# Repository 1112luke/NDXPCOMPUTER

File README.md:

<h1 align="center">⚡️🚀Notre Dame Rocketry Flight Computer🖥️⚡️</h1>

<h2 align="center">F.E.R.B (For Every Rocketry Build) 🤓</h2>

<p align="center">
  </img>
</p>

<h4 align="center">This is the repository for the HARDWARE DESIGN ONLY. Software for the computer can be found <a href="https://github.com/1112luke/NDXP_COMPUTER_SOFTWARE">here</a></h4>

## Introduction

While initially designed and developed for NDXP, all vehicle applications were heavily considered during the process. The result is a computer that is <i>intended</i> to be used for any and all rocketry vehicles!

## Contributing
This repository is open at all times to any member submitting a Pull Request and merging their code directly into the main branch after approval! If you don't know what a Pull Request is, or if this is your first time using github, it is recommended that you watch [this](https://docs.github.com/en/get-started/start-your-journey/hello-world) guide before you begin.

### Requirements
Before you do anything, make sure you:
 - Have [git](https://git-scm.com/downloads) installed on your computer (macos should by default).
 - Have [kicad](https://www.kicad.org/) installed on your computer
 - Are added as a repository contributor (ask a team lead)

To make a contribution, the generall process is:

<b><i>clone/pull → branch → make your changes → add;commit;push → request approval for merge</i></b>

Each step is broken down as follows:

### Clone/Pull 🤖
If this is your first time interacting with this repository on your local machine, execute the following command in the location on your computer you wish to clone the repository to:

```
git clone https://github.com/1112luke/CubeFlightComputer
```

If you have the repository already and wish to begin a new contribution <b><u>it is important that you get the most recent version of the repository: </u></b>

```
git switch main
git pull origin main --rebase
```

### Branch 🪾
Once you have an up to date copy of the repository on your local machine, you will need to create a new branch for your contribution:

```
git branch -c branch-name
```

```
git switch branch-name
```

Feel free to name it whatever you want. Be descriptive!

### Make Your Changes 👨‍💻
At this point, you are free to make whatever changes you want! Any time you are working in your local copy, you do not have to worry about messing up the project. Feel free to delete the entire thing if you want!
 - Experiment
 - Break Things
 - Absolutely Cook 👨‍🍳

<b>THIS IS HOW WE LEARN!!</b>

### Add;Commit;Push 💡
When you are satisfied with your contribution, execute the following steps to push your changes to github for review:

```
git add .
```

```
git commit -m "your-descriptive-message"
```

```
git push origin branch-name
```

Once that is done, your code should be pushed to this repository! The final step is to submit a pull request for your code to the main branch using this website, and it will be reviewed for merge shortly!

### RULE OF THUMB!!
In general, commits to github should be <b>small</b> and <b>frequent</b>! This ensures that everybody is working with the most up to date version of the code!

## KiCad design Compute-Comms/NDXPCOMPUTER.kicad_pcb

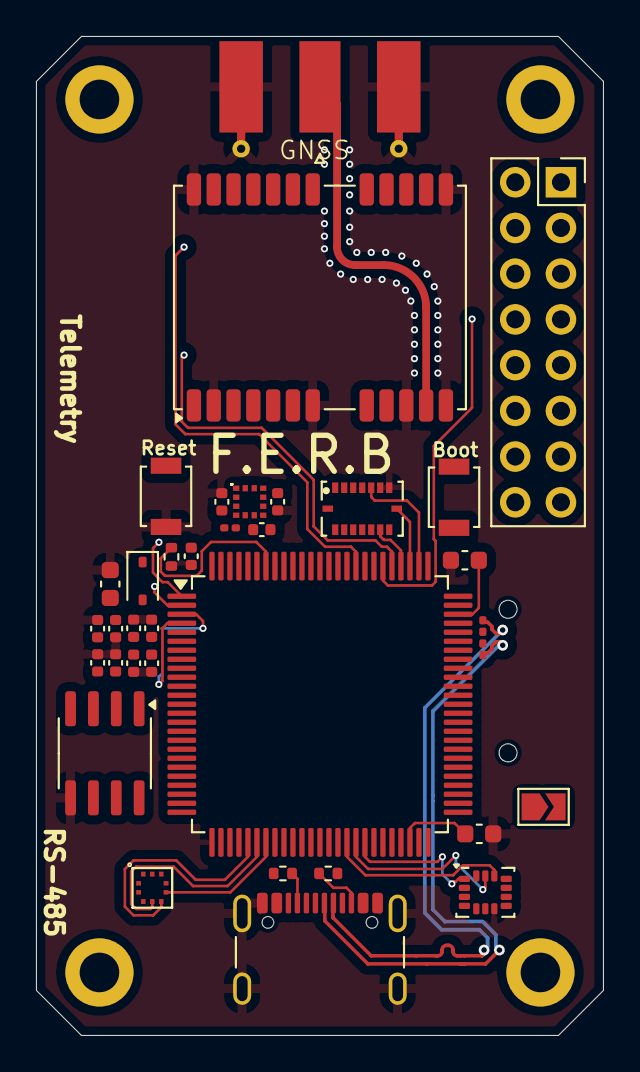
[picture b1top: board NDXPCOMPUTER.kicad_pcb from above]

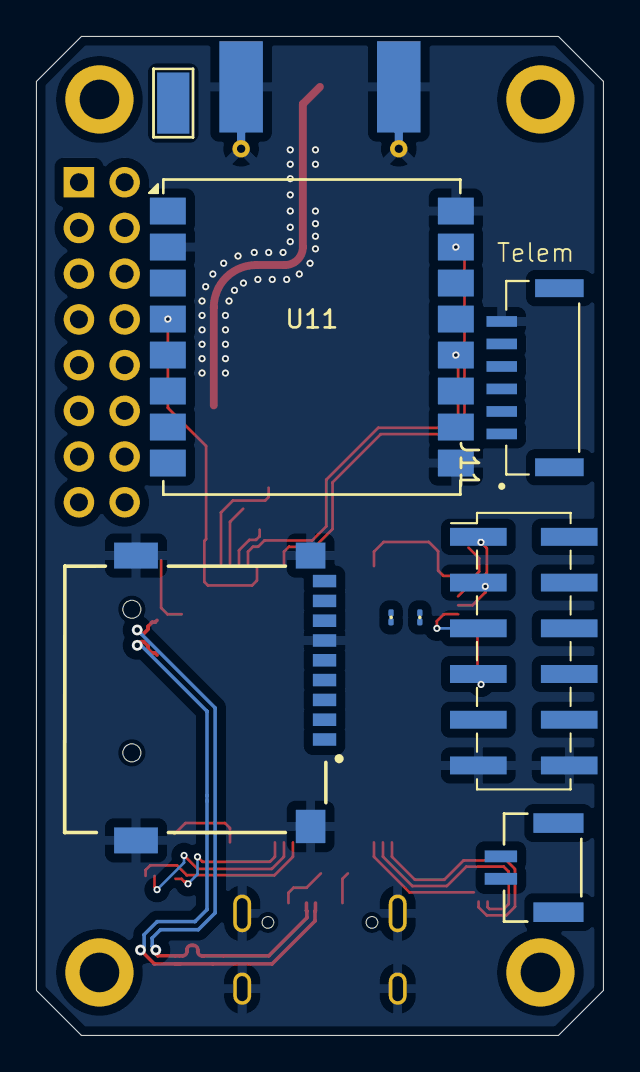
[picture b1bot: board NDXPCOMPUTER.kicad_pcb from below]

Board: 4 copper layers, 31.5 x 55.5 mm, 47 parts (8 on the bottom side), 44 nets.

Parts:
C1: 0.1uF; C_0402_1005Metric
C2, C3, C4, C5, C6, C7, C8, C9, C29, C30: 100nF; C_0402_1005Metric
C10: 4.7uF; C_0603_1608Metric
C11, C12: 2.2uF; C_0603_1608Metric
C17: 220nF; C_0402_1005Metric
C31: 10uF; C_0201_0603Metric
D1: D; D_SOD-323
D2, D3: LED; LED_01005_0402Metric
H1, H2, H3, H4: MountingHole; MountingHole_2.2mm_M2_DIN965_Pad
IC1: IIS2MDCTR
J2: USB_C_Receptacle_USB2.0_16P; USB_C_Receptacle_GCT_USB4105-xx-A_16P_TopMnt_Horizontal
J3: Conn_Coaxial; SMA_Molex_73251-1153_EdgeMount_Horizontal
J4: Conn_01x02; CONN_SM02B-GHS_JST
J9: Conn_01x01; TestPoint_Keystone_5015_Micro-Minature
J11: Conn_01x06; JST_SM06B-GHS-TB_LF__SN_
J12: Conn_02x08_Counter_Clockwise; PinSocket_2x08_P2.54mm_Vertical
J13: Conn_02x06_Odd_Even; PinHeader_2x06_P2.54mm_Vertical_SMD
JP1: SolderJumper_2_Open; SolderJumper-2_P1.3mm_Open_TrianglePad1.0x1.5mm
MICRO_SD1: TF-01A
R1, R2: 5.1k; R_0402_1005Metric
R3: 10k; R_0402_1005Metric
R6, R7: 22; R_0201_0603Metric
SW1, SW2: SW_Push; SW_SPST_B3U-1000P
U1: STM32H723VGTx; LQFP-100_14x14mm_P0.5mm
U2: BMI088; PQFN50P450X300X100-16N
U3: LSM6DSM; LGA-14_3x2.5mm_P0.5mm_LayoutBorder3x4y
U4: BMP581
U5: NEO-M9N; ublox_NEO
U10: SP3485EN; SOIC-8_3.9x4.9mm_P1.27mm
U11: Ai-Thinker-Ra-01; Ai-Thinker-Ra-01-LoRa

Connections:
+3.3V: C2.1, C3.1, C4.1, C5.1, C6.1, C7.1, C8.1, C9.1, C10.1, C29.1, C30.1, C31.1, IC1.3 (CS), IC1.9 (VDD), IC1.10 (VDD_IO), J13.9, SW1.1, U1.6 (VBAT), U1.11 (VDD), U1.20 (VREF+), U1.21 (VDDA), U1.27 (VDD), U1.50 (VDD), U1.75 (VDD), U1.100 (VDD), U2.3 (VDD), U2.11 (VDDIO), U3.5 (VDDIO), U3.8 (VDD), U4.1 (VDDIO), U4.10 (VDD), U5.22 (V_BCKP), U5.23 (VCC), U10.8 (VCC), U11.3 (VDD)
+5V: J11.1, J13.10
/BMI088/CS_ACCEL: U1.76 (PA14(JTCK), U2.14 (CSB1)
/BMI088/CS_GYRO: U1.77 (PA15(JTDI)), U2.5 (CSB2)
/BMI088/SCK: U1.78 (PC10), U2.8 (SCL/SCK)
/BMI088/SDI: U1.36 (PB2), U2.9 (SDA/SDI)
/BMI088/SDO_ACCEL: U1.79 (PC11), U2.10 (SDO2), U2.15 (SDO1)
/BMM350/SCL_MAG: IC1.1 (SCL/SPC), U1.59 (PD12)
/BMM350/SDA_MAG: IC1.4 (SDA/SDI/SDO), U1.60 (PD13)
/BMP581/CS_BARO: U1.32 (PC4), U4.6 (CSB)
/BMP581/SCK_BARO: U1.80 (PC12), U4.2 (SCK/SCL), U11.12 (SCK)
/BMP581/SDI_BARO: U1.31 (PA7), U4.4 (SDI/SDA), U11.14 (MOSI)
/BMP581/SDO_BARO: U1.30 (PA6), U4.5 (SDO/ADR), U11.13 (MISO)
/LSM6DSM/CS_IMU_LOW: U1.41 (PE11), U3.12 (CS)
/LSM6DSM/SCL_IMU_LOW: U1.42 (PE12), U3.13 (SCL)
/LSM6DSM/SDI_IMU_LOW: U1.44 (PE14), U3.14 (SDA)
/LSM6DSM/SDO_IMU_LOW: U1.43 (PE13), U3.1 (SDO/SA0)
/LoRa/CS_LORA: U1.84 (PD3), U11.15 (~NSS)
/LoRa/RST_LORA: U1.81 (PD0), U11.4 (~RESET)
/Peripherals/PYRO_1: J13.1, U1.1 (PE2)
/Peripherals/PYRO_2: J13.3, U1.2 (PE3)
/Peripherals/PYRO_3: J13.5, U1.3 (PE4)
/Peripherals/PYRO_4: J13.7, U1.4 (PE5)
/RS485/DIR_RS485: U1.65 (PC8), U10.2 (~RE), U10.3 (DE)
/RS485/RX_RS485: U1.64 (PC7), U10.1 (RO)
/RS485/TX_RS485: U1.63 (PC6), U10.4 (DI)
D+: J2.A6 (D+), J2.B6 (D+), R7.2
D-: J2.A7 (D-), J2.B7 (D-), R6.2
GND: C1.2, C2.2, C3.2, C4.2, C5.2, C6.2, C7.2, C8.2, C9.2, C10.2, C11.1, C12.1, C17.2, C29.2, C30.2, C31.2, IC1.6 (GND_1), IC1.8 (GND_2), J2.A1 (GND), J2.A12 (GND), J2.B1 (GND), J2.B12 (GND), J2.S1 (SHIELD), J3.2 (Ext), J11.6, J13.11, J13.12, MICRO_SD1.6 (VSS), MICRO_SD1.MP1 (SHIELD), MICRO_SD1.MP2 (SHIELD), MICRO_SD1.MP3 (SHIELD), MICRO_SD1.MP4 (SHIELD), R1.1, R2.2, R3.2, SW2.1, U1.10 (VSS), U1.12 (PH0), U1.19 (VSSA), U1.26 (VSS), U1.49 (VSS), U1.74 (VSS), U1.99 (VSS), U2.2 (NC), U2.4 (GNDA), U2.6 (GNDIO), U2.7 (PS), U3.2 (SDX), U3.3 (SCX), U3.6 (GND), U3.7 (GND), U4.3 (GND), U4.8 (GND), U4.9 (GND), U5.2 (D_SEL), U5.7 (VDD_USB), U5.10 (GND), U5.12 (GND), U5.13 (GND), U5.24 (GND), U10.5 (GND), U11.2 (GND), U11.9 (GND), U11.16 (GND)
unnamed: C11.2, U1.48 (VCAP)
unnamed: C12.2, U1.73 (VCAP)
unnamed: D1.2 (A), J2.A4 (VBUS), J2.A9 (VBUS), J2.B4 (VBUS), J2.B9 (VBUS)
unnamed: C17.1, IC1.5 (C1)
unnamed: J2.A5 (CC1), R1.2
unnamed: J2.B5 (CC2), R2.1
unnamed: J3.1 (In), U5.11 (RF_IN)
unnamed: J4.1, U10.6 (A)
unnamed: J4.2, U10.7 (B)
unnamed: J9.1, U11.1 (ANT)
unnamed: C1.1, JP1.1 (A), SW2.2
unnamed: JP1.2 (B), U1.14 (NRST)
unnamed: R3.1, SW1.2, U1.94 (BOOT0)
unnamed: R6.1, U1.70 (PA11)
unnamed: R7.1, U1.71 (PA12)

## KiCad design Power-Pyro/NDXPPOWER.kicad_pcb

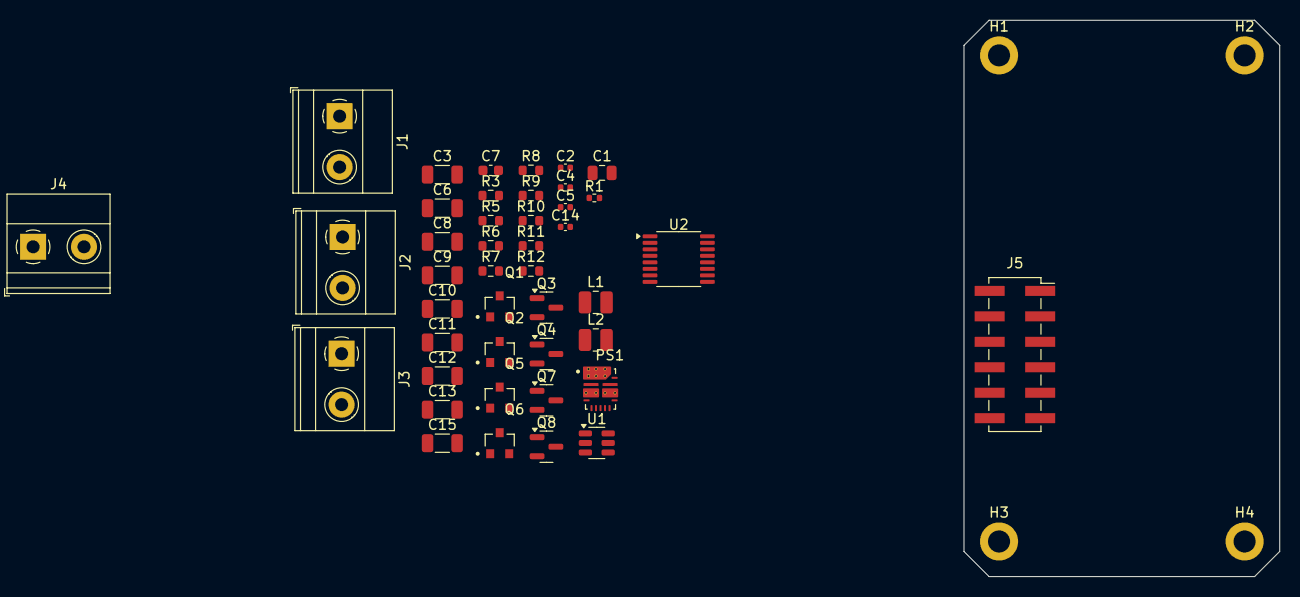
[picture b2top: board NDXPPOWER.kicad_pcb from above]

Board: 2 copper layers, 31.5 x 55.5 mm, 47 parts (0 on the bottom side), 27 nets, no tracks yet.

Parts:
C1: 10uF; C_0805_2012Metric
C2: 470pF; C_0402_1005Metric
C3, C6, C8, C9, C10, C11, C12, C13, C15: 22uF; C_1206_3216Metric
C4, C5, C14: 100nF; C_0402_1005Metric
C7: 2.2uF; C_0603_1608Metric
H1, H2, H3, H4: MountingHole; MountingHole_2.2mm_M2_DIN965_Pad
J1, J2, J3, J4: Conn_01x02; TerminalBlock_Phoenix_MKDS-1,5-2-5.08_1x02_P5.08mm_Horizont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
J5: Conn_02x06_Odd_Even; PinSocket_2x06_P2.54mm_Vertical_SMD
L1: 4.7uH; L_1008_2520Metric
L2: 1.5uH; L_1008_2520Metric
PS1: TPS513885VABR; CONV_TPS513885VABR
Q1, Q2, Q5, Q6: SSM3J328R; SOT95P240X88-3N
Q3, Q4, Q7, Q8: L2N7002SLLT1G; SOT-23
R1: 1k; R_0402_1005Metric
R3, R5, R6, R7, R8, R9, R10, R11, R12: 100k; R_0603_1608Metric
U1: AP63203WU; TSOT-23-6
U2: INA260; TSSOP-16_4.4x5mm_P0.65mm

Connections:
+3.3V: C3.1, C6.1, J5.9, L1.2, PS1.5 (MODE), PS1.6 (EN), U1.1 (FB)
+5V: C9.1, C11.1, C13.1, C15.1, J5.10, L2.2
+BATT: C1.1, C8.1, C10.1, C12.1, C14.1, PS1.1 (VIN), Q1.3 (S), Q2.3 (S), Q5.3 (S), Q6.3 (S), R5.1, R6.1, R9.1, R10.1, U1.2 (EN), U1.3 (IN)
FB: C2.1, C9.2, C11.2, C13.2, C15.2, PS1.8 (VOUT)
GND: C1.2, C3.2, C6.2, C7.1, C8.2, C10.2, C12.2, C14.2, J1.1, J2.1, J3.1, J4.1, J5.11, J5.12, PS1.3 (PGND), PS1.11 (PGND), Q3.3 (S), Q4.3 (S), Q7.3 (S), Q8.3 (S), U1.4 (GND)
unnamed: C2.2, R1.1
unnamed: C5.2, L2.1, PS1.2 (SW), PS1.12 (SW)
unnamed: J1.2, Q1.1 (D)
unnamed: J2.2, Q2.1 (D)
unnamed: J3.2, Q5.1 (D)
unnamed: J4.2, Q6.1 (D)
unnamed: PS1.7 (FB), R1.2
unnamed: PS1.4 (PG), R3.1
unnamed: C7.2, PS1.10 (VCC), R3.2
unnamed: Q1.2 (G), R5.2, R7.1
unnamed: Q2.2 (G), R6.2, R8.1
unnamed: Q3.1 (D), R7.2
unnamed: Q4.1 (D), R8.2
unnamed: Q5.2 (G), R9.2, R11.1
unnamed: Q6.2 (G), R10.2, R12.1
unnamed: Q7.1 (D), R11.2
unnamed: Q8.1 (D), R12.2
unnamed: C4.2, U1.6 (BST)
unnamed: C4.1, L1.1, U1.5 (SW)
unnamed: U2.6 (GND), U2.11 (GND)
unnamed: U2.1 (IN+), U2.2 (IN+), U2.3 (IN+)
unnamed: U2.14 (IN-), U2.15 (IN-), U2.16 (IN-)

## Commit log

2025-09-11 initial
2025-09-13 computer🤓
2025-09-13 sensors📡
2025-09-14 board🏄‍♂️
2025-09-14 ignore😴
2025-09-14 done
2025-09-14 move🛝
2025-09-14 idk what this was
2025-09-14 power docs⚡️
2025-09-15 usb-c🔌
2025-09-16 mcu⚡️
2025-09-16 gps🌎
2025-09-16 test
2025-09-19 Magnetometer🧲
2025-09-19 magnetic🧲
2025-09-20 5v⚡️
2025-09-21 FETS🦈
2025-09-23 computer
2025-09-23 memory🧠
2025-09-23 touchups💅
2025-09-23 LoRa🌊
2025-09-23 routed🛣️
2025-09-25 branches
2025-09-25 rework🗂️
2025-09-25 read
2025-09-25 power🔋
2025-09-25 refactor🧮
2025-09-25 separate⚮
2025-09-25 terminal🚉
2025-09-25 sd♠️
2025-09-25 refactor✖️
2025-09-26 FERBBBB🟣
2025-09-26 baller🏀
2025-09-26 added current chip
2025-09-30 Diff🍐
2025-09-30 some⛓️‍💥
